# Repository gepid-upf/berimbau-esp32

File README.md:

# berimbau-esp32

Berimbau-like toy with gamification to aid with musical rythm and pulse education. It uses an ESP32 as it's main microcontroller. The audio is handled by the 2 DAC channels and is interrupt-based with digital mixing and SFX (muffling effect that emulates the ressonance box of the berimbau based on the distance captured by an URM37). It also uses the SPIFFS for saving the recorded sequences to be repeated by the user.

## Getting Started

### Compiling

You will need ESP-IDF to compile this. Please refer to [ESP-IDF](https://docs.espressif.com/projects/esp-idf/en/latest/get-started/index.html) to install. To compile, clone this repo recursively with all submodules, and run
```
make flash
```

### Assemblying the components

The [schematic](docs/schematic/berimbau.sch) was made using EagleCAD student version. There you can find how the components are connected. If you do not want to download EagleCAD or do not have a license, please refer to this [pdf schematic](docs/schematic/berimbau.pdf).

### Making the PCB

This is completely optional, but recommended. The PCB was made using a Roland EGX-350 router with the software CopperCAM. Please refer to the [PCB project](docs/schematic/berimbau.cam).

### Editing the Flash contents

There is a tool to edit the contents of the flash memory and dump the utilization logs. You can find it at [berimbau-tool-gui](https://github.com/gepid-upf/berimbau-tool-gui).

## Authors

* **Angelo Elias Dalzotto** - *Berimbau Interface and Game, Audio Library, URM37 driver, LED and button control* - [aedalzotto](https://github.com/aedalzotto)

## Acknowledgements

* **Boris Lovosevic** - *[ESP32_TFT_library](https://github.com/loboris/ESP32_TFT_library)* - [loboris](https://github.com/loboris)

## License

This project is licensed under the MIT License - see the [LICENSE.md](LICENSE.md) file for details.

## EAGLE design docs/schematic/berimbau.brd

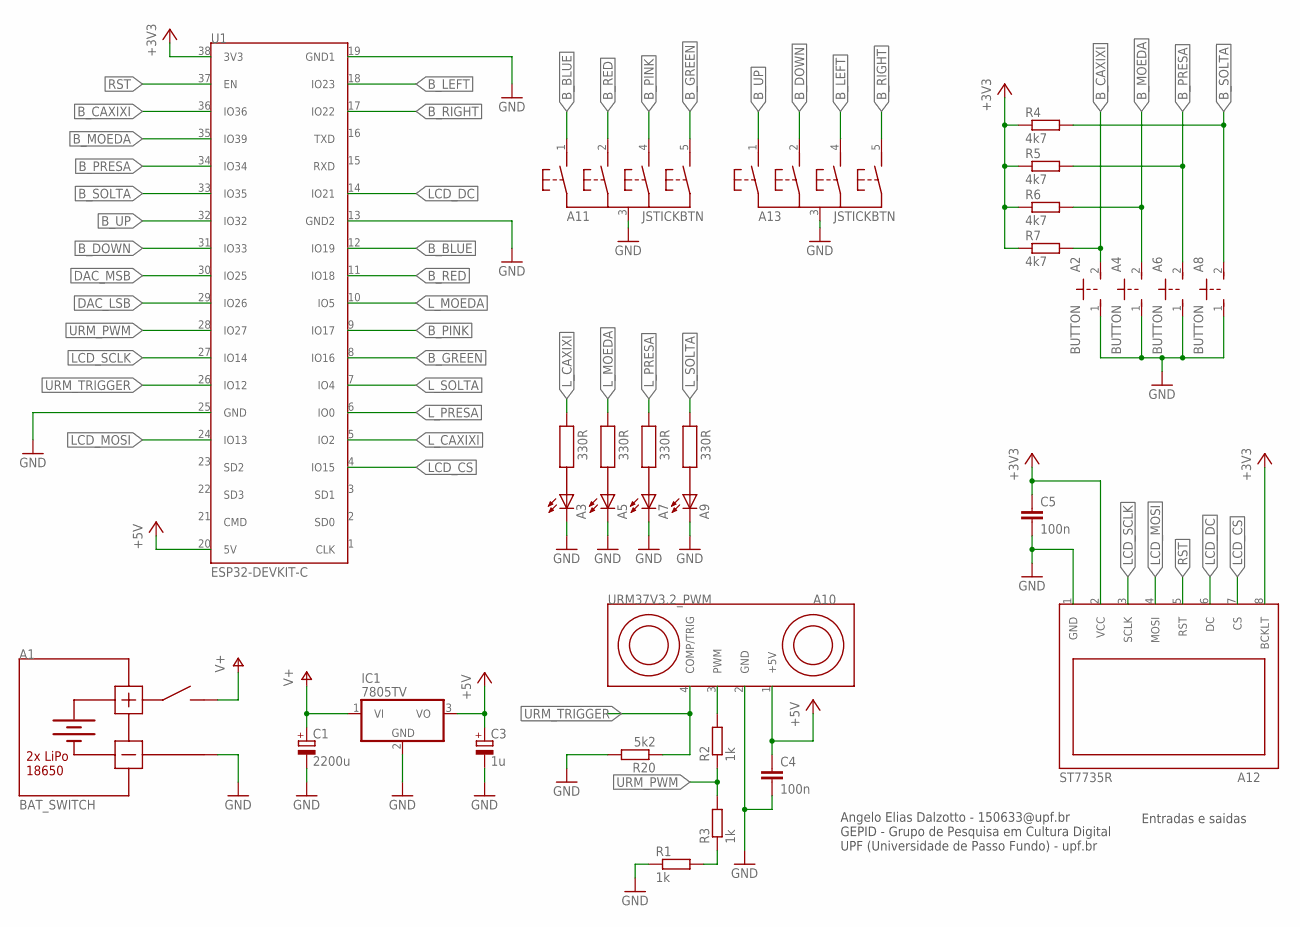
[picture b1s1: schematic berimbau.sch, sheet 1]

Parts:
A1: BAT_SWITCH; 1X02
A2, A4, A6, A8: BUTTON; 1X02
A3, A5, A7, A9: LED; 1X02
A10: URM37V3.2_PWM; 1X04
A11, A13: JSTICKBTN; 1X05
A12: ST7735R; 1X08
C1: 2200u; E3,5-10
C3: 1u; E2-5
C4, C5: 100n; C050-030X075
IC1: 7805TV; TO220V
R1, R2, R3: 1k; 0207/10
R4, R5, R6, R7: 4k7; 0207/10
R20: 5k2; 0207/10
U1: ESP32-DEVKIT-C; ESP32

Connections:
+3V3: A12.2 (VCC), A12.8 (BCKLT), C5.1, R4.1, R5.1, R6.1, R7.1, U1.38 (3V3)
+5V: A10.1 (+5V), C3.+, C4.1, IC1.3 (VO), U1.20 (5V)
B_BLUE: A11.1 (B1), U1.12 (IO19)
B_CAXIXI: A2.2 (S), R7.2, U1.36 (IO36)
B_DOWN: A13.2 (B2), U1.31 (IO33)
B_GREEN: A11.5 (B4), U1.8 (IO16)
B_LEFT: A13.4 (B3), U1.18 (IO23)
B_MOEDA: A4.2 (S), R6.2, U1.35 (IO39)
B_PINK: A11.4 (B3), U1.9 (IO17)
B_PRESA: A6.2 (S), R5.2, U1.34 (IO34)
B_RED: A11.2 (B2), U1.11 (IO18)
B_RIGHT: A13.5 (B4), U1.17 (IO22)
B_SOLTA: A8.2 (S), R4.2, U1.33 (IO35)
B_UP: A13.1 (B1), U1.32 (IO32)
DAC_LSB: U1.29 (IO26); also elsewhere on the board
DAC_MSB: U1.30 (IO25); also elsewhere on the board
GND: A1.2 (-), A2.1, A3.2 (C), A4.1, A5.2 (C), A6.1, A7.2 (C), A8.1, A9.2 (C), A10.2 (GND), A11.3 (COM), A12.1 (GND), A13.3 (COM), C1.-, C3.-, C4.2, C5.2, IC1.2 (GND), R1.1, R20.2, U1.13 (GND2), U1.19 (GND1), U1.25 (GND); also elsewhere on the board
LCD_CS: A12.7 (CS), U1.4 (IO15)
LCD_DC: A12.6 (DC), U1.14 (IO21)
LCD_MOSI: A12.4 (MOSI), U1.24 (IO13)
LCD_SCLK: A12.3 (SCLK), U1.27 (IO14)
L_CAXIXI: A3.1 (A), U1.5 (IO2)
L_MOEDA: A5.1 (A), U1.10 (IO5)
L_PRESA: A7.1 (A), U1.6 (IO0)
L_SOLTA: A9.1 (A), U1.7 (IO4)
unnamed: A10.3 (PWM), R2.2
unnamed: R1.2, R3.1
RST: A12.5 (RST), U1.37 (EN)
URM_PWM: R2.1, R3.2, U1.28 (IO27)
URM_TRIGGER: A10.4 (COMP/TRIG), R20.1, U1.26 (IO12)
V+: A1.1 (+), C1.+, IC1.1 (VI); also elsewhere on the board

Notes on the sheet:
Entradas e saidas
Angelo Elias Dalzotto - 150633@upf.br GEPID - Grupo de Pesquisa em Cultura Digital UPF (Universidade de Passo Fundo) - upf.br

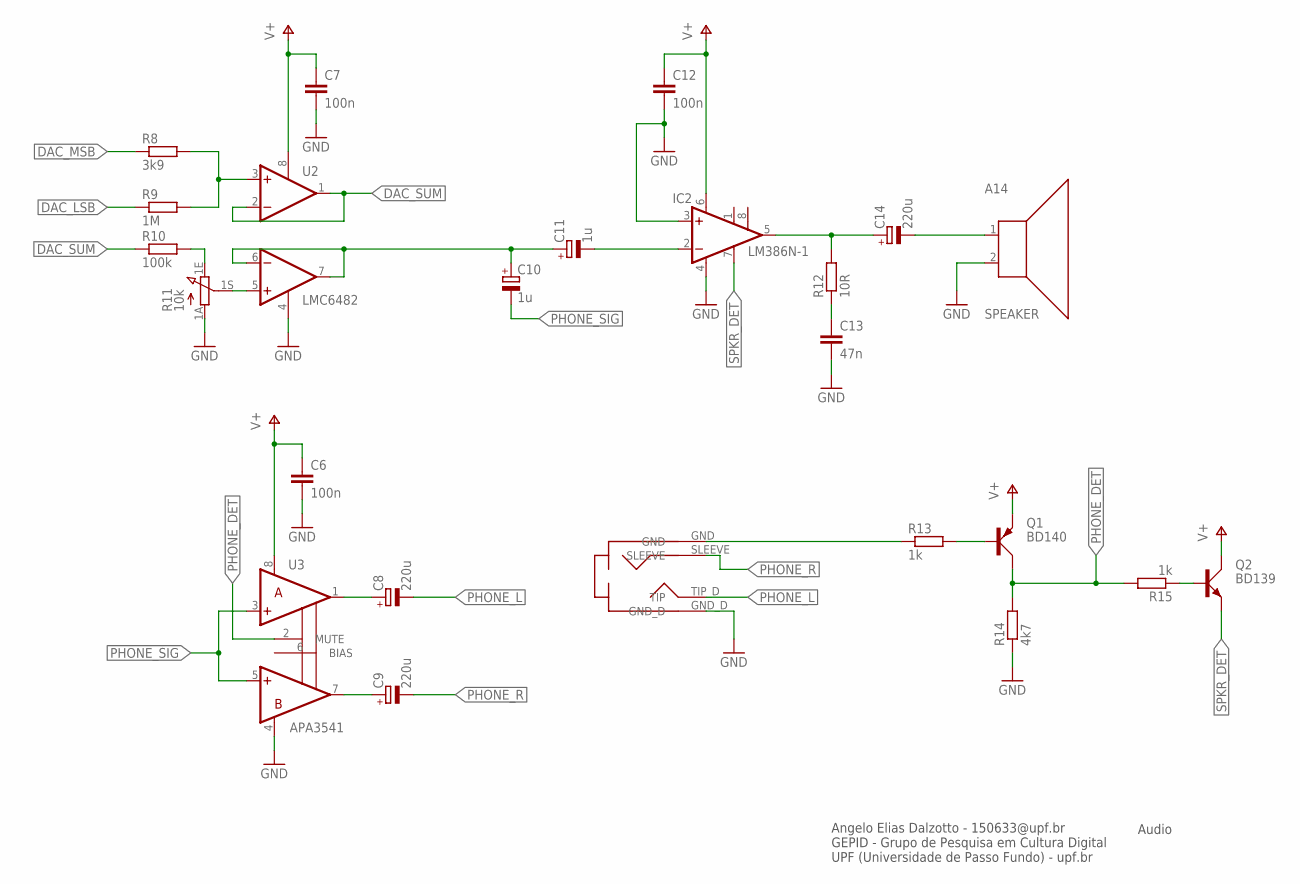
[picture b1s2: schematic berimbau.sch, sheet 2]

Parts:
A14: SPEAKER; 1X02
C6, C7, C12: 100n; C050-030X075
C8, C9: 220u; E2-5
C10, C11: 1u; E2-5
C13: 47n; C050-030X075
C14: 220u; E3,5-10
IC2: LM386N-1; DIL08
J1: P2_RPI; P2_RASPI
Q1: BD140; TO126AV
Q2: BD139; TO126AV
R8: 3k9; 0207/10
R9: 1M; 0207/10
R10: 100k; 0207/10
R11: 10k; PC16S
R12: 10R; 0207/10
R13, R15: 1k; 0207/10
R14: 4k7; 0207/10
U2: LMC6482; DIL08
U3: APA3541; DIL08

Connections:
DAC_LSB: R9.1; also elsewhere on the board
DAC_MSB: R8.1; also elsewhere on the board
DAC_SUM: R10.1, U2.1 (OUT_A), U2.2 (-IN_A)
GND: A14.2 (-), C6.2, C7.2, C12.2, C13.2, IC2.3 (+IN), IC2.4 (GND), J1.GND_D, R11.1A (A), R14.1, U2.4 (V-), U3.4 (GND); also elsewhere on the board
unnamed: R11.1S (S), U2.5 (+IN_B)
unnamed: C10.+, C11.+, U2.6 (-IN_B), U2.7 (OUT_B)
unnamed: R8.2, R9.2, U2.3 (+IN_A)
unnamed: R10.2, R11.1E (E)
unnamed: J1.GND, R13.1
unnamed: C14.+, IC2.5 (OUT), R12.2
unnamed: C13.1, R12.1
unnamed: A14.1 (+), C14.-
unnamed: C8.+, U3.1 (OUT_A)
unnamed: C9.+, U3.7 (OUT_B)
unnamed: Q1.B, R13.2
unnamed: Q2.B, R15.1
PHONE_DET: Q1.C, R14.2, R15.2, U3.2 (MUTE)
PHONE_L: C8.-, J1.TIP_D (TIP)
PHONE_R: C9.-, J1.SLEEVE
PHONE_SIG: C10.-, U3.3 (+IN_A), U3.5 (+IN_B)
SPKR_DET: IC2.7 (BYPASS), Q2.E
SPKR_SIG: C11.-, IC2.2 (-IN)
V+: C6.1, C7.1, C12.1, IC2.6 (VS), Q1.E, Q2.C, U2.8 (V+), U3.8 (VS1); also elsewhere on the board

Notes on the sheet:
Angelo Elias Dalzotto - 150633@upf.br GEPID - Grupo de Pesquisa em Cultura Digital UPF (Universidade de Passo Fundo) - upf.br
Audio

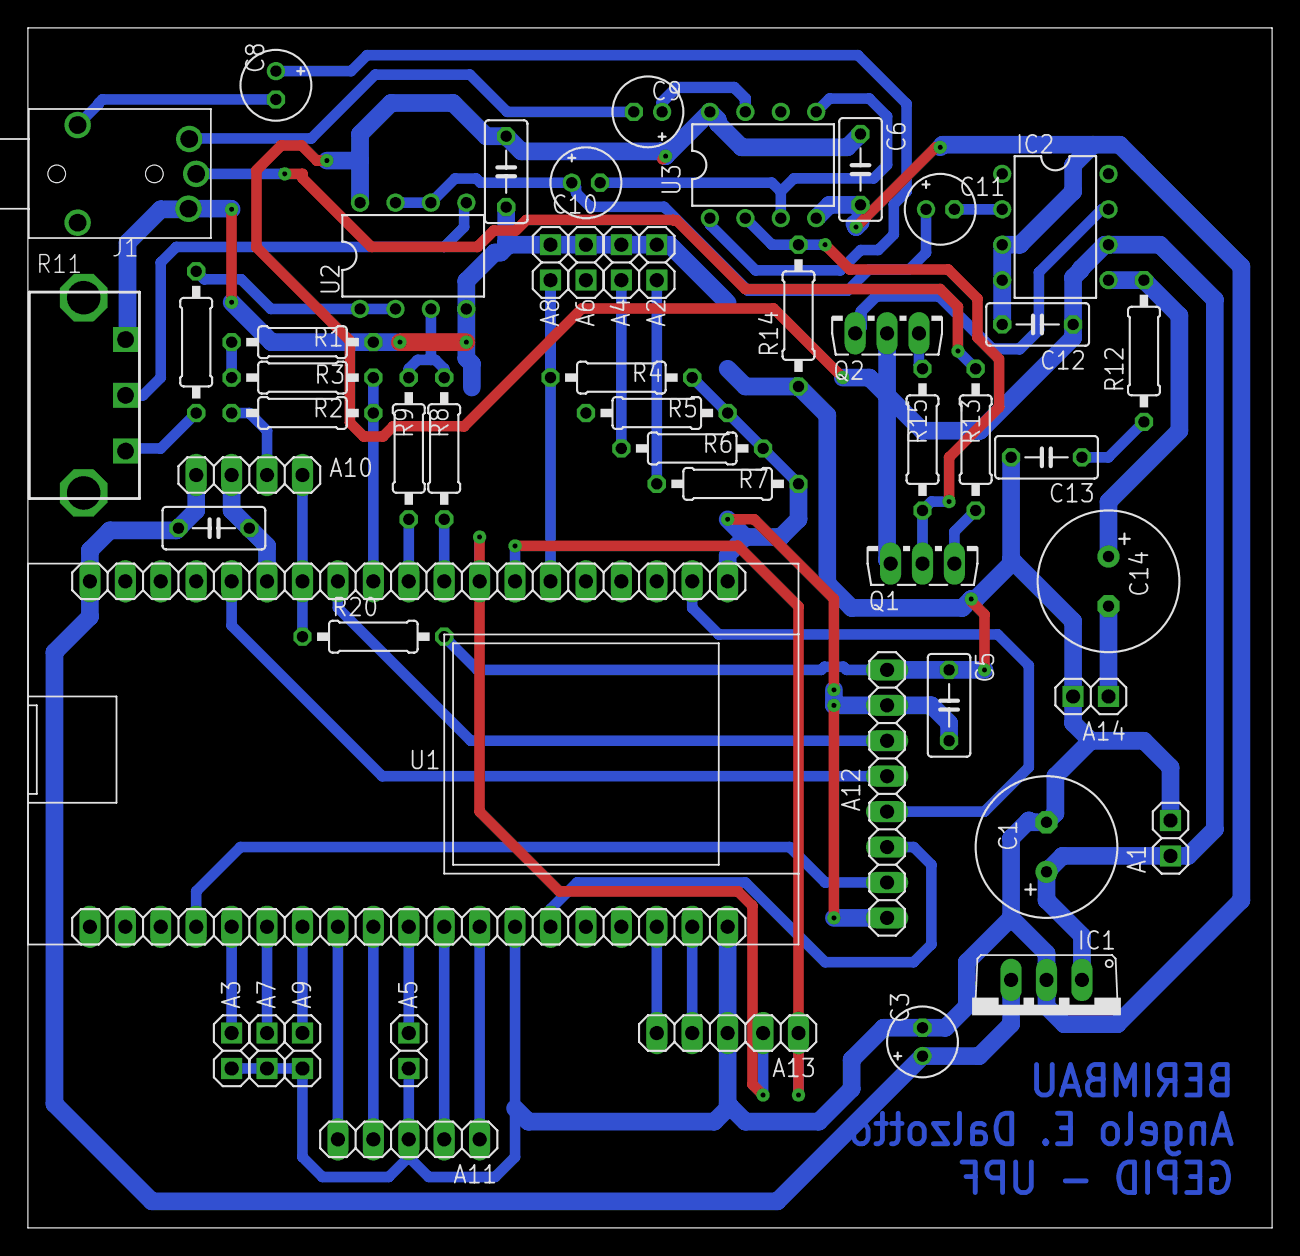
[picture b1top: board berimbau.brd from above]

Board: 2 copper layers, 89.2 x 86.0 mm, 51 parts (0 on the bottom side), 50 nets.

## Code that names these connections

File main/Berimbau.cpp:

/**
 * @file Berimbau.cpp
 * 
 * @author
 * Angelo Elias Dalzotto (150633@upf.br)
 * GEPID - Grupo de Pesquisa em Cultura Digital (gepid.upf.br)
 * Universidade de Passo Fundo (upf.br)
 * 
 * @copyright
 * Copyright 2018 Angelo Elias Dalzotto
 * 
 * @brief Berimbau is a digital toy to help kids with music learning.
 */

#include <freertos/FreeRTOS.h>
#include <freertos/task.h>

#include <Game.h>
#include <Interface.h>
#include <Audio.h>
#include <Button.h>
#include <Led.h>

#include "moeda.h" // Just for testing
#include "presa.h"
#include "caxixi.h"
#include "solta.h"

// Members that are added to a static vector inside the class must be initialized here.
static Button b_moeda(GPIO_NUM_39);
static Button b_caxixi(GPIO_NUM_36);
static Button b_presa(GPIO_NUM_35);
static Button b_solta(GPIO_NUM_34);

static Button b_blue(GPIO_NUM_32);
static Button b_red(GPIO_NUM_23);
static Button b_green(GPIO_NUM_22);
static Button b_pink(GPIO_NUM_33);

static Button b_left(GPIO_NUM_18);
static Button b_right(GPIO_NUM_16);
static Button b_up(GPIO_NUM_17);
static Button b_down(GPIO_NUM_19);

static Audio DRAM_ATTR a_moeda(moeda_data, moeda_length);
static Audio DRAM_ATTR a_caxixi(caxixi_data, caxixi_length, false);
static Audio DRAM_ATTR a_solta(solta_data, solta_length);
static Audio DRAM_ATTR a_presa(presa_data, presa_length);

static Led l_moeda(GPIO_NUM_4);
static Led l_caxixi(GPIO_NUM_5);
static Led l_presa(GPIO_NUM_0);
static Led l_solta(GPIO_NUM_2);

static const char* TAG = "MAIN";

extern "C" void app_main()
{
    Interface::pre_init(); // Init the LCD and the Semaphore first for loading screen

    Interface::set_button(&b_blue, Interface::Direction::D_X);
    Interface::set_button(&b_red, Interface::Direction::D_O);
    Interface::set_button(&b_green, Interface::Direction::D_T);
    Interface::set_button(&b_pink, Interface::Direction::D_S);

    Interface::set_button(&b_right, Interface::Direction::D_RIGHT);
    Interface::set_button(&b_left, Interface::Direction::D_LEFT);
    Interface::set_button(&b_up, Interface::Direction::D_UP);
    Interface::set_button(&b_down, Interface::Direction::D_DOWN);

    Game::set_button(&b_moeda, Game::Instrument::MOEDA);
    Game::set_button(&b_caxixi, Game::Instrument::CAXIXI);
    Game::set_button(&b_presa, Game::Instrument::PRESA);
    Game::set_button(&b_solta, Game::Instrument::SOLTA);

    Game::set_audio(&a_moeda, Game::Instrument::MOEDA);
    Game::set_audio(&a_caxixi, Game::Instrument::CAXIXI);
    Game::set_audio(&a_presa, Game::Instrument::PRESA);
    Game::set_audio(&a_solta, Game::Instrument::SOLTA);

    Game::set_led(&l_moeda, Game::Instrument::MOEDA);
    Game::set_led(&l_caxixi, Game::Instrument::CAXIXI);
    Game::set_led(&l_presa, Game::Instrument::PRESA);
    Game::set_led(&l_solta, Game::Instrument::SOLTA);

    xTaskCreate(Interface::task, "Interface Task", 16384, nullptr, 6, nullptr);

    Audio::init();  // TimerG0 Timer0 interrupt 44.1KHz for Audio.

    xTaskCreate(Button::task, "Button_task", 2048, nullptr, 11, nullptr);   // Updates the Button status.
    xTaskCreate(Game::task, "Game task", 8192, nullptr, 10, nullptr);
    xTaskCreate(Led::task, "LED Task", 2048, nullptr, 8, nullptr);  // Sets and updates led status
    xTaskCreate(Game::urm_task, "URM Task", 2048, nullptr, 7, nullptr); // Sets the muffle cutoff based on URM
}

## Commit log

2019-02-21 added lcd, interface and game
2019-02-21 added schematics
2019-03-14 update pins for new board
2019-03-14 added boot pull-down
2019-03-18 fixed pin out
2019-03-21 fixed partition table
2019-03-27 ensure binary write mode
2019-03-27 fixed pinout
2019-04-17 fixed samples and variable sizes
2019-04-17 dont erase presets
2019-04-25 Create LICENSE
2019-05-14 added more logging and changed led logic
2019-05-21 removed pull down on piezo
2019-05-21 create pdf schematic
